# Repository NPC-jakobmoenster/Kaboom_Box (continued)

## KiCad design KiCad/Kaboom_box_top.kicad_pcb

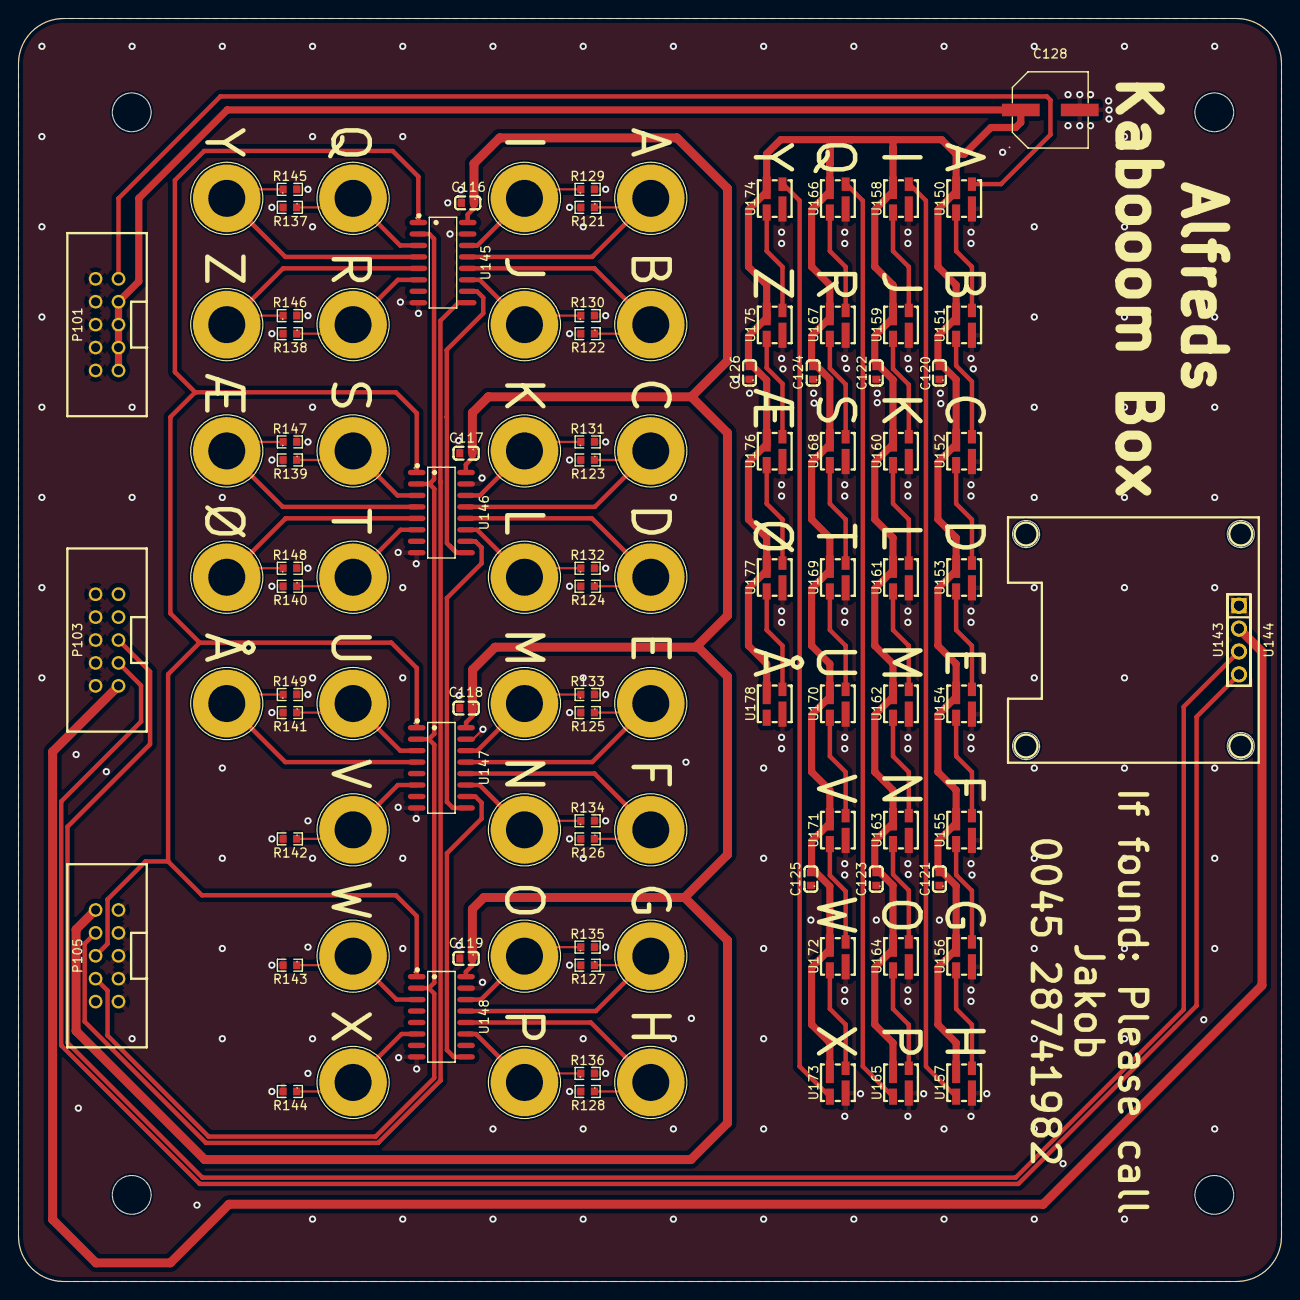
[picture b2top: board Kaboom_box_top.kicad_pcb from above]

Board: 2 copper layers, 140.0 x 140.0 mm, 113 parts (0 on the bottom side), 70 nets.

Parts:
B102: Board
C116, C117, C118, C119, C120, C121, C122, C123, C124, C125, C126: CC0603KRX7R9BB104; C0603
C128: RVT0J102M0810; CAP-SMD_BD8.0-L8.3-W8.3-FD
H105, H106, H107, H108: MountingHole; MountingHole_4.3mm_M4
J130, J131, J132, J133, J134, J135, J136, J137, J138, J139, J140, J141, J142, J143, J144, J145, J146, J147, J148, J149, J150, J151, J152, J153, J154, J155, J156, J157, J158: 2mm_clamp; 2mm testlead, screw-clamp
P101, P103, P105: HDR-IDC-2_54-2X5P; IDC-TH_10P-P2.54_C5665
R121, R122, R123, R124, R125, R126, R127, R128, R129, R130, R131, R132, R133, R134, R135, R136, R137, R138, R139, R140, R141, R142, R143, R144, R145, R146, R147, R148, R149: 0603WAF1202T5E; R0603
U143: PZ254V-11-04P_C2691448; HDR-TH_4P-P2.54-V-M
U144: HS96L03W2C03; OLED-TH_L27.8-W27.2-P2.54_C9900033791
U145, U146, U147, U148: 74HC165D,653; SOIC-16_L9.9-W3.9-P1.27-LS6.0-BL
U150, U151, U152, U153, U154, U155, U156, U157, U158, U159, U160, U161, U162, U163, U164, U165, U166, U167, U168, U169, U170, U171, U172, U173, U174, U175, U176, U177, U178: WS2812E-MINI-X1; LED-SMD_4P-L3.7-W3.5-P1.75-BR-SK6812MINI

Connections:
Board_0-/I2C1_SDA_LID: P103.3, U143.4, U144.4 (SDA)
Board_0-/I2C_SCL_LID: P103.5, U143.3, U144.3 (SCL)
Board_0-/SPI0_CSn_LID: P105.6, U145.1 (PL#), U146.1 (PL#), U147.1 (PL#), U148.1 (PL#)
Board_0-/SPI0_RX_LID: P105.8, U145.9 (Q7)
Board_0-/SPI0_SCK_LID: P105.4, U145.2 (CP), U146.2 (CP), U147.2 (CP), U148.2 (CP)
Board_0-/Top/+3.3V_OLED: P103.1, U143.2, U144.2 (VCC)
Board_0-/Top/+3.3V_SHIFT: C116.1, C117.1, C118.1, C119.1, P105.10, U145.16 (VCC), U146.16 (VCC), U147.16 (VCC), U148.16 (VCC)
Board_0-/Top/GND: C116.2, C117.2, C118.2, C119.2, C120.1, C121.1, C122.1, C123.1, C124.1, C125.1, C126.1, C128.2, P101.2, P101.4, P101.6, P101.8, P101.10, P103.2, P103.4, P103.6, P103.8, P103.10, P105.1, P105.3, P105.5, P105.7, P105.9, R121.2, R122.2, R123.2, R124.2, R125.2, R126.2, R127.2, R128.2, R129.2, R130.2, R131.2, R132.2, R133.2, R134.2, R135.2, R136.2, R137.2, R138.2, R139.2, R140.2, R141.2, R142.2, R143.2, R144.2, R145.2, R146.2, R147.2, R148.2, R149.2, U143.1, U144.1 (GND), U145.8 (GND), U145.15 (CE#), U146.8 (GND), U146.15 (CE#), U147.8 (GND), U147.15 (CE#), U148.8 (GND), U148.15 (CE#), U150.4 (GND), U151.4 (GND), U152.4 (GND), U153.4 (GND), U154.4 (GND), U155.4 (GND), U156.4 (GND), U157.4 (GND), U158.4 (GND), U159.4 (GND), U160.4 (GND), U161.4 (GND), U162.4 (GND), U163.4 (GND), U164.4 (GND), U165.4 (GND), U166.4 (GND), U167.4 (GND), U168.4 (GND), U169.4 (GND), U170.4 (GND), U171.4 (GND), U172.4 (GND), U173.4 (GND), U174.4 (GND), U175.4 (GND), U176.4 (GND), U177.4 (GND), U178.4 (GND)
Board_0-/Top/LED_DATA_IN: P101.9, U150.1 (DI)
Board_0-/Top/Shift_Parallel_to_Serial/J130: J130.1, R121.1, U145.13 (D2)
Board_0-/Top/Shift_Parallel_to_Serial/J131: J131.1, R122.1, U145.12 (D1)
Board_0-/Top/Shift_Parallel_to_Serial/J132: J132.1, R123.1, U146.13 (D2)
Board_0-/Top/Shift_Parallel_to_Serial/J133: J133.1, R124.1, U146.12 (D1)
Board_0-/Top/Shift_Parallel_to_Serial/J134: J134.1, R125.1, U147.13 (D2)
Board_0-/Top/Shift_Parallel_to_Serial/J135: J135.1, R126.1, U147.12 (D1)
Board_0-/Top/Shift_Parallel_to_Serial/J136: J136.1, R127.1, U148.13 (D2)
Board_0-/Top/Shift_Parallel_to_Serial/J137: J137.1, R128.1, U148.12 (D1)
Board_0-/Top/Shift_Parallel_to_Serial/J138: J138.1, R129.1, U145.14 (D3)
Board_0-/Top/Shift_Parallel_to_Serial/J139: J139.1, R130.1, U145.11 (D0)
Board_0-/Top/Shift_Parallel_to_Serial/J140: J140.1, R131.1, U146.14 (D3)
Board_0-/Top/Shift_Parallel_to_Serial/J141: J141.1, R132.1, U146.11 (D0)
Board_0-/Top/Shift_Parallel_to_Serial/J142: J142.1, R133.1, U147.14 (D3)
Board_0-/Top/Shift_Parallel_to_Serial/J143: J143.1, R134.1, U147.11 (D0)
Board_0-/Top/Shift_Parallel_to_Serial/J144: J144.1, R135.1, U148.14 (D3)
Board_0-/Top/Shift_Parallel_to_Serial/J145: J145.1, R136.1, U148.11 (D0)
Board_0-/Top/Shift_Parallel_to_Serial/J146: J146.1, R137.1, U145.3 (D4)
Board_0-/Top/Shift_Parallel_to_Serial/J147: J147.1, R138.1, U145.6 (D7)
Board_0-/Top/Shift_Parallel_to_Serial/J148: J148.1, R139.1, U146.3 (D4)
Board_0-/Top/Shift_Parallel_to_Serial/J149: J149.1, R140.1, U146.6 (D7)
Board_0-/Top/Shift_Parallel_to_Serial/J150: J150.1, R141.1, U147.3 (D4)
Board_0-/Top/Shift_Parallel_to_Serial/J151: J151.1, R142.1, U147.6 (D7)
Board_0-/Top/Shift_Parallel_to_Serial/J152: J152.1, R143.1, U148.3 (D4)
Board_0-/Top/Shift_Parallel_to_Serial/J153: J153.1, R144.1, U148.6 (D7)
Board_0-/Top/Shift_Parallel_to_Serial/J154: J154.1, R145.1, U145.4 (D5)
Board_0-/Top/Shift_Parallel_to_Serial/J155: J155.1, R146.1, U145.5 (D6)
Board_0-/Top/Shift_Parallel_to_Serial/J156: J156.1, R147.1, U146.4 (D5)
Board_0-/Top/Shift_Parallel_to_Serial/J157: J157.1, R148.1, U146.5 (D6)
Board_0-/Top/Shift_Parallel_to_Serial/J158: J158.1, R149.1, U147.4 (D5)
Board_0-/Top/Shift_Parallel_to_Serial/SER_IN_1: U147.10 (DS), U148.9 (Q7)
Board_0-/Top/Shift_Parallel_to_Serial/SER_IN_2: U146.10 (DS), U147.9 (Q7)
Board_0-/Top/Shift_Parallel_to_Serial/SER_IN_3: U145.10 (DS), U146.9 (Q7)
Board_0-/Top/VDD: C120.2, C121.2, C122.2, C123.2, C124.2, C125.2, C126.2, C128.1, P101.1, P101.3, P101.5, P101.7, U150.2 (VDD), U151.2 (VDD), U152.2 (VDD), U153.2 (VDD), U154.2 (VDD), U155.2 (VDD), U156.2 (VDD), U157.2 (VDD), U158.2 (VDD), U159.2 (VDD), U160.2 (VDD), U161.2 (VDD), U162.2 (VDD), U163.2 (VDD), U164.2 (VDD), U165.2 (VDD), U166.2 (VDD), U167.2 (VDD), U168.2 (VDD), U169.2 (VDD), U170.2 (VDD), U171.2 (VDD), U172.2 (VDD), U173.2 (VDD), U174.2 (VDD), U175.2 (VDD), U176.2 (VDD), U177.2 (VDD), U178.2 (VDD)
Board_0-Net-(U150-DO): U150.3 (DO), U151.1 (DI)
Board_0-Net-(U151-DO): U151.3 (DO), U152.1 (DI)
Board_0-Net-(U152-DO): U152.3 (DO), U153.1 (DI)
Board_0-Net-(U153-DO): U153.3 (DO), U154.1 (DI)
Board_0-Net-(U154-DO): U154.3 (DO), U155.1 (DI)
Board_0-Net-(U155-DO): U155.3 (DO), U156.1 (DI)
Board_0-Net-(U156-DO): U156.3 (DO), U157.1 (DI)
Board_0-Net-(U157-DO): U157.3 (DO), U158.1 (DI)
Board_0-Net-(U158-DO): U158.3 (DO), U159.1 (DI)
Board_0-Net-(U159-DO): U159.3 (DO), U160.1 (DI)
Board_0-Net-(U160-DO): U160.3 (DO), U161.1 (DI)
Board_0-Net-(U161-DO): U161.3 (DO), U162.1 (DI)
Board_0-Net-(U162-DO): U162.3 (DO), U163.1 (DI)
Board_0-Net-(U163-DO): U163.3 (DO), U164.1 (DI)
Board_0-Net-(U164-DO): U164.3 (DO), U165.1 (DI)
Board_0-Net-(U165-DO): U165.3 (DO), U166.1 (DI)
Board_0-Net-(U166-DO): U166.3 (DO), U167.1 (DI)
Board_0-Net-(U167-DO): U167.3 (DO), U168.1 (DI)
Board_0-Net-(U168-DO): U168.3 (DO), U169.1 (DI)
Board_0-Net-(U169-DO): U169.3 (DO), U170.1 (DI)
Board_0-Net-(U170-DO): U170.3 (DO), U171.1 (DI)
Board_0-Net-(U171-DO): U171.3 (DO), U172.1 (DI)
Board_0-Net-(U172-DO): U172.3 (DO), U173.1 (DI)
Board_0-Net-(U173-DO): U173.3 (DO), U174.1 (DI)
Board_0-Net-(U174-DO): U174.3 (DO), U175.1 (DI)
Board_0-Net-(U175-DO): U175.3 (DO), U176.1 (DI)
Board_0-Net-(U176-DO): U176.3 (DO), U177.1 (DI)
Board_0-Net-(U177-DO): U177.3 (DO), U178.1 (DI)

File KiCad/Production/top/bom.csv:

Comment,Designator,Footprint,LCSC
HDR-IDC-2_54-2X5P,"P101,P103,P105",IDC-TH_10P-P2.54_C5665,C5665
RVT0J102M0810,C128,CAP-SMD_BD8.0-L8.3-W8.3-FD,C42851
HS96L03W2C03,U144,OLED-TH_L27.8-W27.2-P2.54_C9900033791,C5248080
WS2812E-MINI-X1,"U150,U151,U152,U153,U154,U155,U156,U157,U158,U159,U160,U161,U162,U163,U164,U165,U166,U167,U168,U169,U170,U171,U172,U173,U174,U175,U176,U177,U178",LED-SMD_4P-L3.7-W3.5-P1.75-BR-SK6812MINI,C4154871
CC0603KRX7R9BB104,"C116,C117,C118,C119,C120,C121,C122,C123,C124,C125,C126",C0603,C14663
2mm_clamp,"J130,J131,J132,J133,J134,J135,J136,J137,J138,J139,J140,J141,J142,J143,J144,J145,J146,J147,J148,J149,J150,J151,J152,J153,J154,J155,J156,J157,J158","Kaboom_box:2mm testlead, screw-clamp",
"74HC165D,653","U145,U146,U147,U148",SOIC-16_L9.9-W3.9-P1.27-LS6.0-BL,C5613

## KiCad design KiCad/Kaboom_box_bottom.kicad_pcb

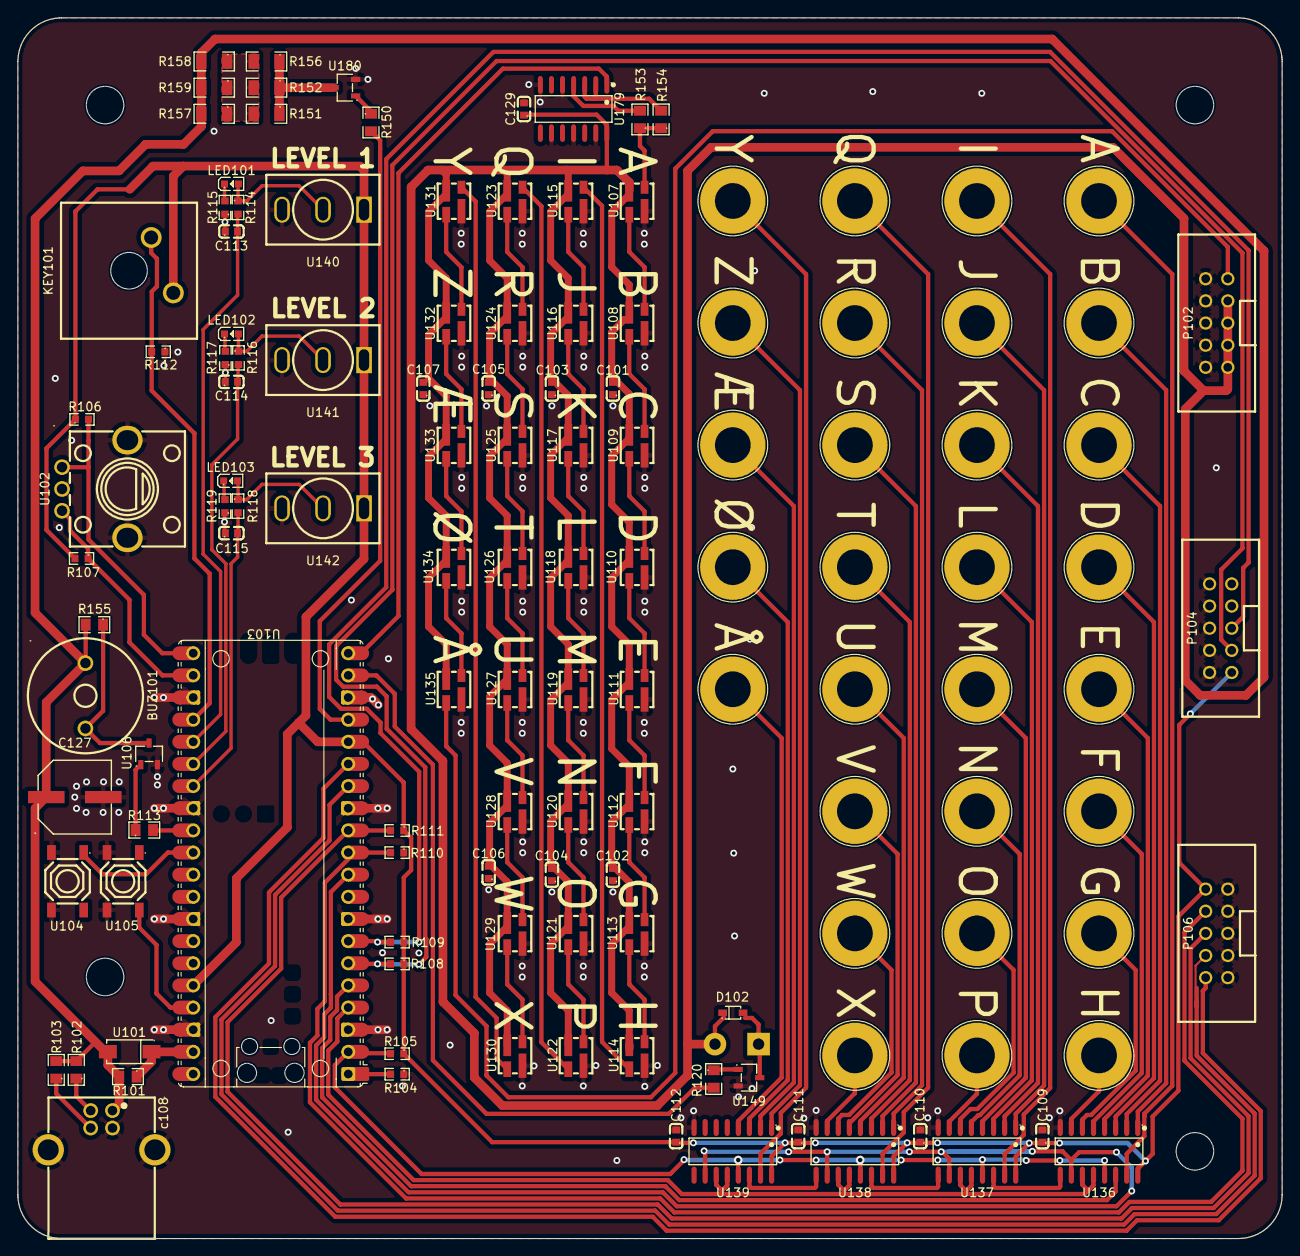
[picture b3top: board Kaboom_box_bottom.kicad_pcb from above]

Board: 2 copper layers, 145.0 x 140.0 mm, 136 parts (1 on the bottom side), 106 nets.

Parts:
B101: Board
BUZ101: ZL-YDW1207-4005PA-7_5; BUZ-TH_BD12.6-P7.50-D0.9
C101, C102, C103, C104, C105, C106, C107, C109, C110, C111, C112, C129: CC0603KRX7R9BB104; C0603
C113, C114, C115: CL10B102KB8NNNC; C0603
C127: RVT0J102M0810; CAP-SMD_BD8.0-L8.3-W8.3-FD
D102: 1N5819WS; SOD-323_L1.8-W1.3-LS2.5-RD
H101, H102, H103, H104: MountingHole; MountingHole_4.3mm_M4
J101, J102, J103, J104, J105, J106, J107, J108, J109, J110, J111, J112, J113, J114, J115, J116, J117, J118, J119, J120, J121, J122, J123, J124, J125, J126, J127, J128, J129: 2mm_clamp; 2mm testlead, screw-clamp
J162: Screw_Terminal_01x02; TerminalBlock_Phoenix_MKDS-1,5-2_1x02_P5.00mm_Horizontal
KEY101: CPG151101D214; KEY-TH_CPG151101D21X
LED101, LED102, LED103: KT-0603R; LED0603-RD
P102, P104, P106: HDR-IDC-2_54-2X5P; IDC-TH_10P-P2.54_C5665
R101, R102, R103, R113, R120, R150, R153, R154: 0805W8F0000T5E; R0805
R104, R105, R110, R111: 0603WAF1003T5E; R0603
R106, R107, R108, R109, R112: 0603WAF1002T5E; R0603
R114, R116, R118: 0603WAF100JT5E; R0603
R115, R117, R119: 0603WAF2000T5E; R0603
R151, R152, R156, R157, R158, R159: 1206W4F1000T5E; R1206
R155: 0805W8F2000T5E; R0805
U101: SS54_C22452; SMA_L4.4-W2.8-LS5.4-R-RD
U102: EC12E1220813; SW-TH_EC12E1220813
U103: RaspberryPi_Pico; RaspberryPi_Pico_Common_No_Keepout
U104, U105: TS-1187A-B-A-B; SW-SMD_4P-L5.1-W5.1-P3.70-LS6.5-TL-2
U106, U149, U180: AO3400A; SOT-23-3_L2.9-W1.6-P1.90-LS2.8-BR
U107, U108, U109, U110, U111, U112, U113, U114, U115, U116, U117, U118, U119, U120, U121, U122, U123, U124, U125, U126, U127, U128, U129, U130, U131, U132, U133, U134, U135: WS2812E-MINI-X1; LED-SMD_4P-L3.7-W3.5-P1.75-BR-SK6812MINI
U136, U137, U138, U139: 74HC595D,118; SOIC-16_L9.9-W3.9-P1.27-LS6.0-BL
U140, U141, U142: MT-0-103-F001-T000-RS+PJ; SW-TH_MT-0-103-A101-M200-RS
U179: 74HC14D,653; SOIC-14_L8.7-W3.9-P1.27-LS6.0-BL
c108: USB-B-Female-TH_C46393; USB-B_TH_BF90

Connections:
Board_0-/Bottom/+3.3V: C109.1, C110.1, C111.1, C112.1, KEY101.2, P104.1, P106.10, R105.1, R106.1, R107.2, R108.1, R109.1, R111.1, U103.16 (GPIO12), U103.36 (3V3), U136.16 (VCC), U137.16 (VCC), U138.16 (VCC), U139.16 (VCC), U140.1, U141.1, U142.1
Board_0-/Bottom/BUZZER: R113.2, U103.29 (GPIO22)
Board_0-/Bottom/CLK: R107.1, U102.B, U103.22 (GPIO17)
Board_0-/Bottom/DT: R106.2, U102.A, U103.21 (GPIO16)
Board_0-/Bottom/LED_DATA_IN: U103.20 (GPIO15), U179.1 (1A)
Board_0-/Bottom/LED_DATA_OUT: P102.9, U135.3 (DO)
Board_0-/Bottom/LEDs Sheet/LED_DATA_IN: R153.1, R154.1, U107.1 (DI)
Board_0-/Bottom/LVL1: C113.2, R114.2, U103.25 (GPIO19)
Board_0-/Bottom/LVL2: C114.2, R116.2, U103.26 (GPIO20)
Board_0-/Bottom/LVL3: C115.2, R118.2, U103.27 (GPIO21)
Board_0-/Bottom/POWER_DRAIN: R150.2, U103.17 (GPIO13)
Board_0-/Bottom/RUMBLE: R120.2, U103.19 (GPIO14)
Board_0-/Bottom/SPI0_CSn: R105.2, U103.2 (GPIO1), U136.13 (OE#), U137.13 (OE#), U138.13 (OE#), U139.13 (OE#)
Board_0-/Bottom/SPI0_RST: U103.10 (GPIO7), U136.10 (MR#), U137.10 (MR#), U138.10 (MR#), U139.10 (MR#)
Board_0-/Bottom/SPI0_RX: R104.2, U103.1 (GPIO0)
Board_0-/Bottom/SPI0_SCK: U103.4 (GPIO2), U136.11 (SHCP), U136.12 (STCP), U137.11 (SHCP), U137.12 (STCP), U138.11 (SHCP), U138.12 (STCP), U139.11 (SHCP), U139.12 (STCP)
Board_0-/Bottom/SPI0_TX: U103.5 (GPIO3), U136.14 (DS)
Board_0-/Bottom/START: KEY101.1, R112.2, U103.24 (GPIO18)
Board_0-/Bottom/Shift_Serial_to_Parallel/SERIAL_IN_2: U136.9 (Q7S), U137.14 (DS)
Board_0-/Bottom/Shift_Serial_to_Parallel/SERIAL_IN_3: U137.9 (Q7S), U138.14 (DS)
Board_0-/Bottom/Shift_Serial_to_Parallel/SERIAL_IN_4: U138.9 (Q7S), U139.14 (DS)
Board_0-/Bottom/VDD: BUZ101.1, C101.2, C102.2, C103.2, C104.2, C105.2, C106.2, C107.2, C127.1, C129.1, D102.1 (K), J162.2, P102.1, P102.3, P102.5, P102.7, R101.2, R102.2, R103.2, R155.2, R157.2, R158.2, R159.2, U101.1 (A), U107.2 (VDD), U108.2 (VDD), U109.2 (VDD), U110.2 (VDD), U111.2 (VDD), U112.2 (VDD), U113.2 (VDD), U114.2 (VDD), U115.2 (VDD), U116.2 (VDD), U117.2 (VDD), U118.2 (VDD), U119.2 (VDD), U120.2 (VDD), U121.2 (VDD), U122.2 (VDD), U123.2 (VDD), U124.2 (VDD), U125.2 (VDD), U126.2 (VDD), U127.2 (VDD), U128.2 (VDD), U129.2 (VDD), U130.2 (VDD), U131.2 (VDD), U132.2 (VDD), U133.2 (VDD), U134.2 (VDD), U135.2 (VDD), U179.14 (VCC), c108.1 (VCC)
Board_0-/I2C1_SDA_BOT: P104.3, R108.2, U103.6 (GPIO4)
Board_0-/I2C_SCL_BOT: P104.5, R109.2, U103.7 (GPIO5)
Board_0-/SPI0_CSn_BOT: P106.6, R111.2, U103.12 (GPIO9)
Board_0-/SPI0_RX_BOT: P106.8, R110.2, U103.11 (GPIO8)
Board_0-/SPI0_SCK_BOT: P106.4, U103.14 (GPIO10)
Board_0-/SPI0_TX_BOT: P106.2, U103.15 (GPIO11)
Board_0-GND: C101.1, C102.1, C103.1, C104.1, C105.1, C106.1, C107.1, C109.2, C110.2, C111.2, C112.2, C113.1, C114.1, C115.1, C127.2, C129.2, P102.2, P102.4, P102.6, P102.8, P102.10, P104.2, P104.4, P104.6, P104.8, P104.10, P106.1, P106.3, P106.5, P106.7, P106.9, R104.1, R110.1, R112.1, R115.1, R117.1, R119.1, U102.C, U102.D, U102.E, U103.3 (GND), U103.8 (GND), U103.13 (GND), U103.18 (GND), U103.23 (GND), U103.28 (GND), U103.33 (AGND), U103.38 (GND), U104.3 (C), U104.4 (D), U105.3 (C), U105.4 (D), U106.2 (S), U107.4 (GND), U108.4 (GND), U109.4 (GND), U110.4 (GND), U111.4 (GND), U112.4 (GND), U113.4 (GND), U114.4 (GND), U115.4 (GND), U116.4 (GND), U117.4 (GND), U118.4 (GND), U119.4 (GND), U120.4 (GND), U121.4 (GND), U122.4 (GND), U123.4 (GND), U124.4 (GND), U125.4 (GND), U126.4 (GND), U127.4 (GND), U128.4 (GND), U129.4 (GND), U130.4 (GND), U131.4 (GND), U132.4 (GND), U133.4 (GND), U134.4 (GND), U135.4 (GND), U136.8 (GND), U137.8 (GND), U138.8 (GND), U139.8 (GND), U140.3, U141.3, U142.3, U149.2 (S), U179.5 (3A), U179.7 (GND), U179.9 (4A), U179.11 (5A), U179.13 (6A), U180.2 (S), c108.4 (GND), c108.5 (EH)
Board_0-Net-(D102-A): D102.2 (A), J162.1, U149.3 (D)
Board_0-Net-(J101-Pin_1): J101.1, U136.15 (Q0)
Board_0-Net-(J102-Pin_1): J102.1, U136.7 (Q7)
Board_0-Net-(J103-Pin_1): J103.1, U137.1 (Q1)
Board_0-Net-(J104-Pin_1): J104.1, U136.1 (Q1)
Board_0-Net-(J105-Pin_1): J105.1, U137.2 (Q2)
Board_0-Net-(J106-Pin_1): J106.1, U137.15 (Q0)
Board_0-Net-(J107-Pin_1): J107.1, U136.2 (Q2)
Board_0-Net-(J108-Pin_1): J108.1, U137.3 (Q3)
Board_0-Net-(J109-Pin_1): J109.1, U136.3 (Q3)
Board_0-Net-(J110-Pin_1): J110.1, U137.4 (Q4)
Board_0-Net-(J111-Pin_1): J111.1, U136.4 (Q4)
Board_0-Net-(J112-Pin_1): J112.1, U137.5 (Q5)
Board_0-Net-(J113-Pin_1): J113.1, U136.5 (Q5)
Board_0-Net-(J114-Pin_1): J114.1, U137.6 (Q6)
Board_0-Net-(J115-Pin_1): J115.1, U136.6 (Q6)
Board_0-Net-(J116-Pin_1): J116.1, U137.7 (Q7)
Board_0-Net-(J117-Pin_1): J117.1, U138.1 (Q1)
Board_0-Net-(J118-Pin_1): J118.1, U139.1 (Q1)
Board_0-Net-(J119-Pin_1): J119.1, U138.2 (Q2)
Board_0-Net-(J120-Pin_1): J120.1, U138.15 (Q0)
Board_0-Net-(J121-Pin_1): J121.1, U139.2 (Q2)
Board_0-Net-(J122-Pin_1): J122.1, U139.15 (Q0)
Board_0-Net-(J123-Pin_1): J123.1, U138.3 (Q3)
Board_0-Net-(J124-Pin_1): J124.1, U139.3 (Q3)
Board_0-Net-(J125-Pin_1): J125.1, U138.4 (Q4)
Board_0-Net-(J126-Pin_1): J126.1, U139.4 (Q4)
Board_0-Net-(J127-Pin_1): J127.1, U138.5 (Q5)
Board_0-Net-(J128-Pin_1): J128.1, U138.6 (Q6)
Board_0-Net-(J129-Pin_1): J129.1, U138.7 (Q7)
Board_0-Net-(LED101-A): LED101.2 (A), R114.1, U140.2
Board_0-Net-(LED101-K): LED101.1 (K), R115.2
Board_0-Net-(LED102-A): LED102.2 (A), R116.1, U141.2
Board_0-Net-(LED102-K): LED102.1 (K), R117.2
Board_0-Net-(LED103-A): LED103.2 (A), R118.1, U142.2
Board_0-Net-(LED103-K): LED103.1 (K), R119.2
Board_0-Net-(R151-Pad2): R151.2, R152.2, R156.2, R157.1, R158.1, R159.1
Board_0-Net-(U101-K): R101.1, U101.2 (K), U103.39 (VSYS)
Board_0-Net-(U103-3V3_EN): U103.37 (3V3_EN), U105.2 (B)
Board_0-Net-(U103-RUN): U103.30 (RUN), U104.1 (A)
Board_0-Net-(U106-D): BUZ101.2, R155.1, U106.3 (D)
Board_0-Net-(U106-G): R113.1, U106.1 (G)
Board_0-Net-(U107-DO): U107.3 (DO), U108.1 (DI)
Board_0-Net-(U108-DO): U108.3 (DO), U109.1 (DI)
Board_0-Net-(U109-DO): U109.3 (DO), U110.1 (DI)
Board_0-Net-(U110-DO): U110.3 (DO), U111.1 (DI)
Board_0-Net-(U111-DO): U111.3 (DO), U112.1 (DI)
Board_0-Net-(U112-DO): U112.3 (DO), U113.1 (DI)
Board_0-Net-(U113-DO): U113.3 (DO), U114.1 (DI)
Board_0-Net-(U114-DO): U114.3 (DO), U115.1 (DI)
Board_0-Net-(U115-DO): U115.3 (DO), U116.1 (DI)
Board_0-Net-(U116-DO): U116.3 (DO), U117.1 (DI)
Board_0-Net-(U117-DO): U117.3 (DO), U118.1 (DI)
Board_0-Net-(U118-DO): U118.3 (DO), U119.1 (DI)
Board_0-Net-(U119-DO): U119.3 (DO), U120.1 (DI)
Board_0-Net-(U120-DO): U120.3 (DO), U121.1 (DI)
Board_0-Net-(U121-DO): U121.3 (DO), U122.1 (DI)
Board_0-Net-(U122-DO): U122.3 (DO), U123.1 (DI)
Board_0-Net-(U123-DO): U123.3 (DO), U124.1 (DI)
Board_0-Net-(U124-DO): U124.3 (DO), U125.1 (DI)
Board_0-Net-(U125-DO): U125.3 (DO), U126.1 (DI)
Board_0-Net-(U126-DO): U126.3 (DO), U127.1 (DI)
Board_0-Net-(U127-DO): U127.3 (DO), U128.1 (DI)
Board_0-Net-(U128-DO): U128.3 (DO), U129.1 (DI)
Board_0-Net-(U129-DO): U129.3 (DO), U130.1 (DI)
Board_0-Net-(U130-DO): U130.3 (DO), U131.1 (DI)
Board_0-Net-(U131-DO): U131.3 (DO), U132.1 (DI)
Board_0-Net-(U132-DO): U132.3 (DO), U133.1 (DI)
Board_0-Net-(U133-DO): U133.3 (DO), U134.1 (DI)
Board_0-Net-(U134-DO): U134.3 (DO), U135.1 (DI)
Board_0-Net-(U149-G): R120.1, U149.1 (G)
Board_0-Net-(U179-1Y): R154.2, U179.2 (1Y), U179.3 (2A)
Board_0-Net-(U179-2Y): R153.2, U179.4 (2Y)
Board_0-Net-(U180-D): R151.1, R152.1, R156.1, U180.3 (D)
Board_0-Net-(U180-G): R150.1, U180.1 (G)
Board_0-Net-(c108-D+): R103.1, c108.3 (D+)
Board_0-Net-(c108-D-): R102.1, c108.2 (D-)

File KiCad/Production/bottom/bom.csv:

Comment,Designator,Footprint,LCSC
HDR-IDC-2_54-2X5P,"P102,P104,P106",IDC-TH_10P-P2.54_C5665,C5665
RVT0J102M0810,C127,CAP-SMD_BD8.0-L8.3-W8.3-FD,C42851
WS2812E-MINI-X1,"U107,U108,U109,U110,U111,U112,U113,U114,U115,U116,U117,U118,U119,U120,U121,U122,U123,U124,U125,U126,U127,U128,U129,U130,U131,U132,U133,U134,U135",LED-SMD_4P-L3.7-W3.5-P1.75-BR-SK6812MINI,C4154871
CC0603KRX7R9BB104,"C101,C102,C103,C104,C105,C106,C107,C109,C110,C111,C112",C0603,C14663
2mm_clamp,"J101,J102,J103,J104,J105,J106,J107,J108,J109,J110,J111,J112,J113,J114,J115,J116,J117,J118,J119,J120,J121,J122,J123,J124,J125,J126,J127,J128,J129","Kaboom_box:2mm testlead, screw-clamp",
0603WAF1002T5E,"R106,R107,R108,R109,R112",R0603,C25804
0603WAF1003T5E,"R104,R105,R110,R111",R0603,C25803
1N5819WS,"D101,D102",SOD-323_L1.8-W1.3-LS2.5-RD,C191023
Screw_Terminal_01x02,J162,"TerminalBlock_Phoenix:TerminalBlock_Phoenix_MKDS-1,5-2_1x02_P5.00mm_Horizontal",
AO3400A,"U106,U149",SOT-23-3_L2.9-W1.6-P1.90-LS2.8-BR,C20917
CPG151101D214,KEY101,KEY-TH_CPG151101D21X,C400232
0805W8F0000T5E,"R113,R120",R0805,C17477
EC12E1220813,U102,SW-TH_EC12E1220813,C129727
TS-1187A-B-A-B,"U104,U105",SW-SMD_4P-L5.1-W5.1-P3.70-LS6.5-TL-2,C318884
RaspberryPi_Pico,U103,Module_RaspberryPi_Pico:RaspberryPi_Pico_Common_No_Keepout,
USB-B-Female-TH_C46393,c108,USB-B_TH_BF90,C46393
ZL-YDW1207-4005PA-7_5,BUZ101,BUZ-TH_BD12.6-P7.50-D0.9,C219725
SS54_C22452,U101,SMA_L4.4-W2.8-LS5.4-R-RD,C22452
0603WAF100JT5E,"R114,R116,R118",R0603,C22859
0603WAF2000T5E,"R115,R117,R119",R0603,C8218
KT-0603R,"LED101,LED102,LED103",LED0603-RD,C2286
0603B152K500NT,"C113,C114,C115",C0603,C1595
MT-0-103-F001-T000-RS+PJ,"U140,U141,U142",SW-TH_MT-0-103-A101-M200-RS,C1788498
"74HC595D,118","U136,U137,U138,U139",SOIC-16_L9.9-W3.9-P1.27-LS6.0-BL,C5947

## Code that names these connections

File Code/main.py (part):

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running = False             # Flag for handling if the bomb is started or not.

# PIN setups
lvl1            = Pin(19, Pin.IN)   # input level pin 1
lvl2            = Pin(20, Pin.IN)   # input level pin 2
lvl3            = Pin(21, Pin.IN)   # input level pin 3
startBtn        = Pin(18, Pin.IN)   # Start button
letterOutSck    = Pin(2)            # SPI for letter out, Clock
letterOutMosi   = Pin(3)            # SPI for letter out, MOSI
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oledI2cScl      = Pin(5)            # I2C for OLED screen, Clock (SSD1306)
oledI2cSda      = Pin(4)            # I2C for OLED screen, Data (SSD1306)
onBoardLED      = Pin("LED", Pin.OUT) # PICO on board LED for debugging
npPin           = Pin(15, Pin.OUT)  # GPIO15 to output to drive NeoPixels (digital output)
buzzerPin       = Pin(22, Pin.OUT)           # GPIO22 to output to drive buzzer (digital output)
encoderClk      = 17                # GPIO number for rotary encoder Clock
encoderDt       = 16                # GPIO number for rotary encoder Data
rumble          = Pin(14, Pin.OUT, value=0)         # Pin to enable motor 
powerDrainPin   = Pin(13, Pin.OUT, value=0)         # Pin to enable motor


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
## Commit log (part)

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2023-09-08 Initial commit of the PCBs - WIP
2023-09-08 Update to TOP pcb - 2mm holes placement and routing
2023-09-11 WIP on Bottom
2023-09-11 Layout wip
2023-09-13 Ready for review
2023-09-14 Updated to generate JLCPCB files
2023-10-09 PCB V1
2023-10-09 VScode running
2023-12-12 First draft done - missing comments
2023-12-12 UPdated outline + added pull down resistors on input of shifts
2023-12-14 Updates for V2
2024-01-20 Working - encoder can stall program
2024-05-02 First production
2025-10-16 Updated to not use adressable LED. Sch only
2025-10-16 Ready for PCB layout with discreet LEDs
